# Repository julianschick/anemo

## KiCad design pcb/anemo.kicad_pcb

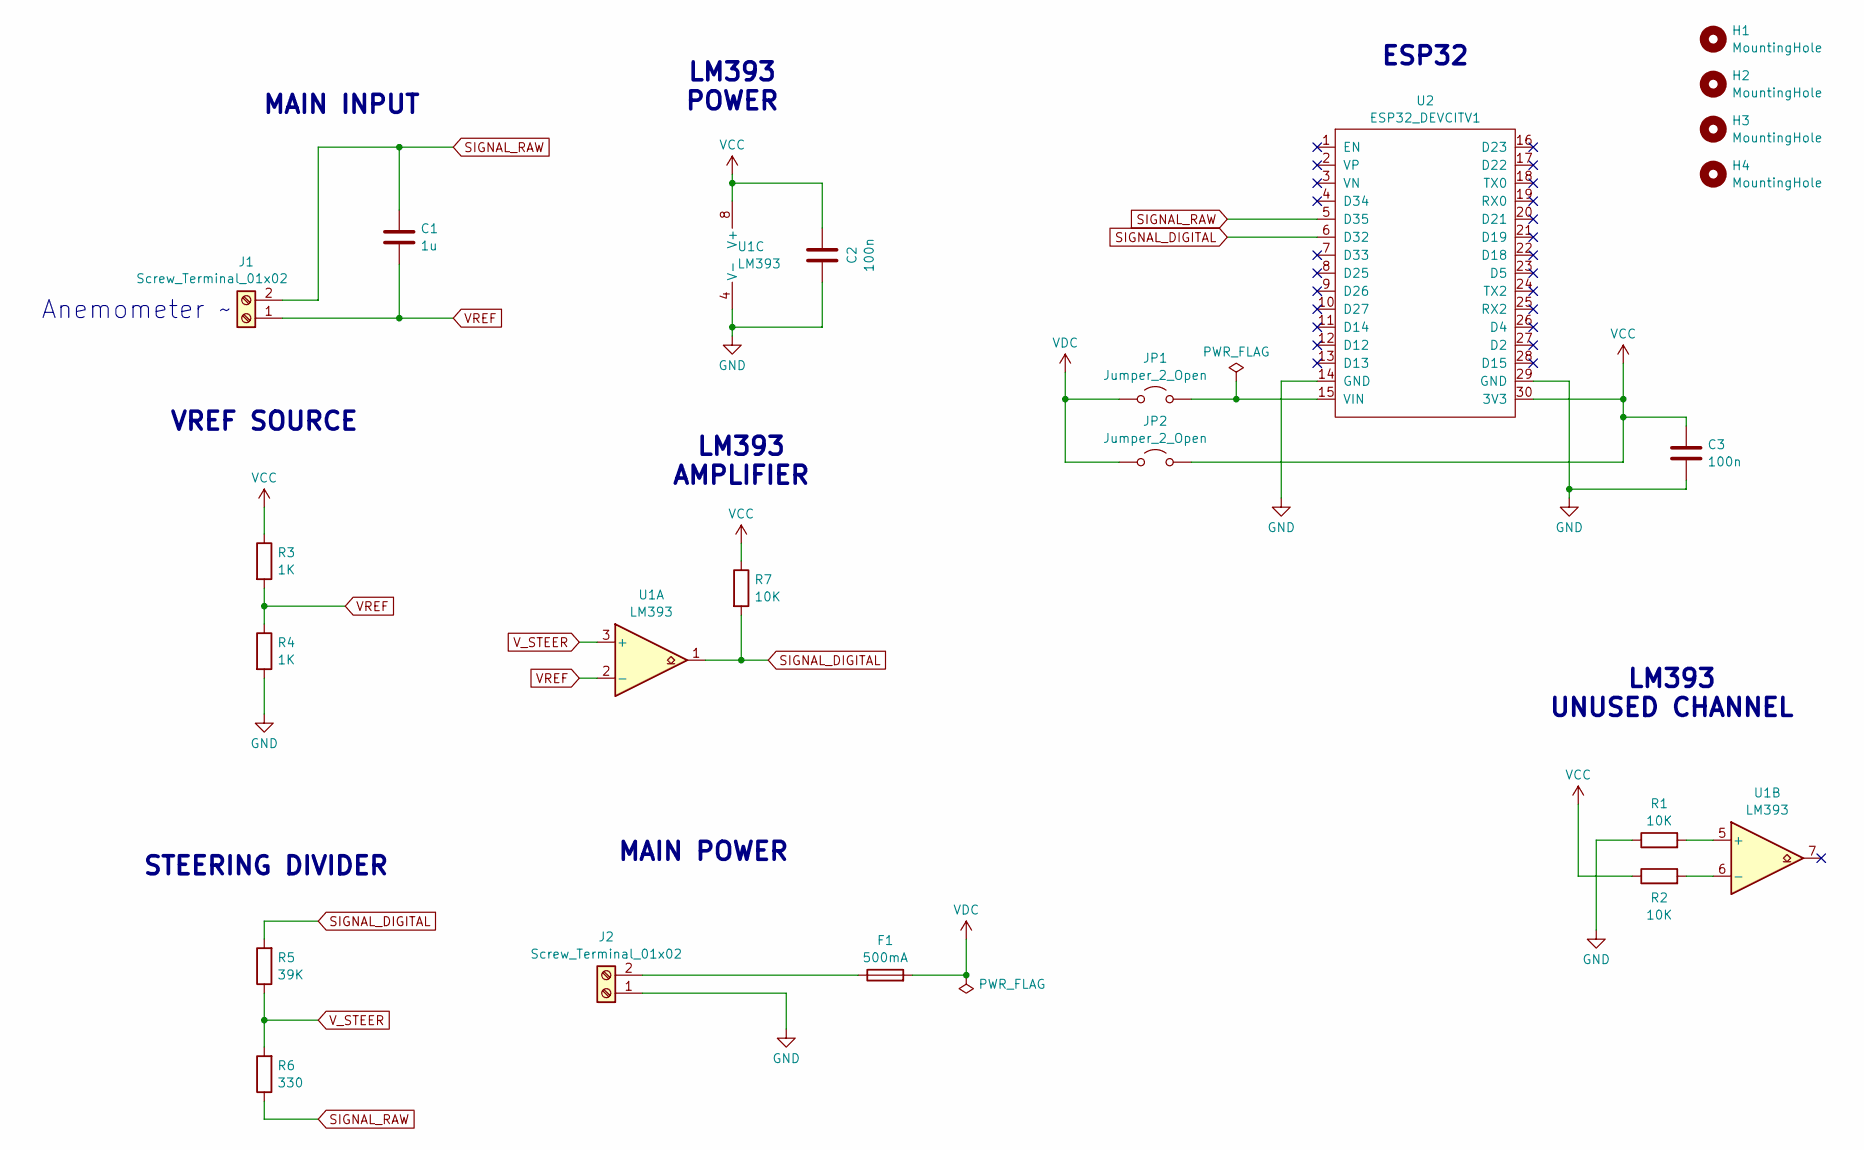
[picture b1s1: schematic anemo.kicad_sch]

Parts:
C1: 1u; C_Disc_D5.0mm_W2.5mm_P5.00mm
C2, C3: 100n; C_Disc_D5.0mm_W2.5mm_P5.00mm
F1: 500mA; Fuseholder_TR5_Littelfuse_No560_No460
H1, H2, H3, H4: MountingHole; MountingHole_3.2mm_M3_ISO7380
J1, J2: Screw_Terminal_01x02; TerminalBlock_MetzConnect_Type055_RT01502HDWU_1x02_P5.00mm_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
JP1, JP2: Jumper_2_Open; PinHeader_1x02_P2.54mm_Vertical
R1, R2, R7: 10K; R_Axial_DIN0207_L6.3mm_D2.5mm_P7.62mm_Horizontal
R3, R4: 1K; R_Axial_DIN0207_L6.3mm_D2.5mm_P7.62mm_Horizontal
R5: 39K; R_Axial_DIN0207_L6.3mm_D2.5mm_P7.62mm_Horizontal
R6: 330; R_Axial_DIN0207_L6.3mm_D2.5mm_P7.62mm_Horizontal
U1: LM393; DIP-8_W7.62mm
U2: ESP32_DEVCITV1; ESP32_DEVKITV1

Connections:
GND: C2.2, C3.2, J2.1, R1.1, R4.2, U1.4 (V-), U2.14 (GND), U2.29 (GND)
unnamed: F1.1, J2.2
unnamed: JP1.2 (B), U2.15 (VIN)
unnamed: R1.2, U1.5 (+)
unnamed: R2.2, U1.6 (-)
SIGNAL_DIGITAL: R5.2, R7.2, U1.1, U2.6 (D32)
SIGNAL_RAW: C1.1, J1.2, R6.1, U2.5 (D35)
VCC: C2.1, C3.1, JP2.2 (B), R2.1, R3.1, R7.1, U1.8 (V+), U2.30 (3V3)
VDC: F1.2, JP1.1 (A), JP2.1 (A)
VREF: C1.2, J1.1, R3.2, R4.1, U1.2 (-)
V_STEER: R5.1, R6.2, U1.3 (+)

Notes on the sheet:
LM393 POWER
ESP32
Anemometer ~
MAIN INPUT
STEERING DIVIDER
VREF SOURCE
LM393 AMPLIFIER
MAIN POWER
LM393 UNUSED CHANNEL

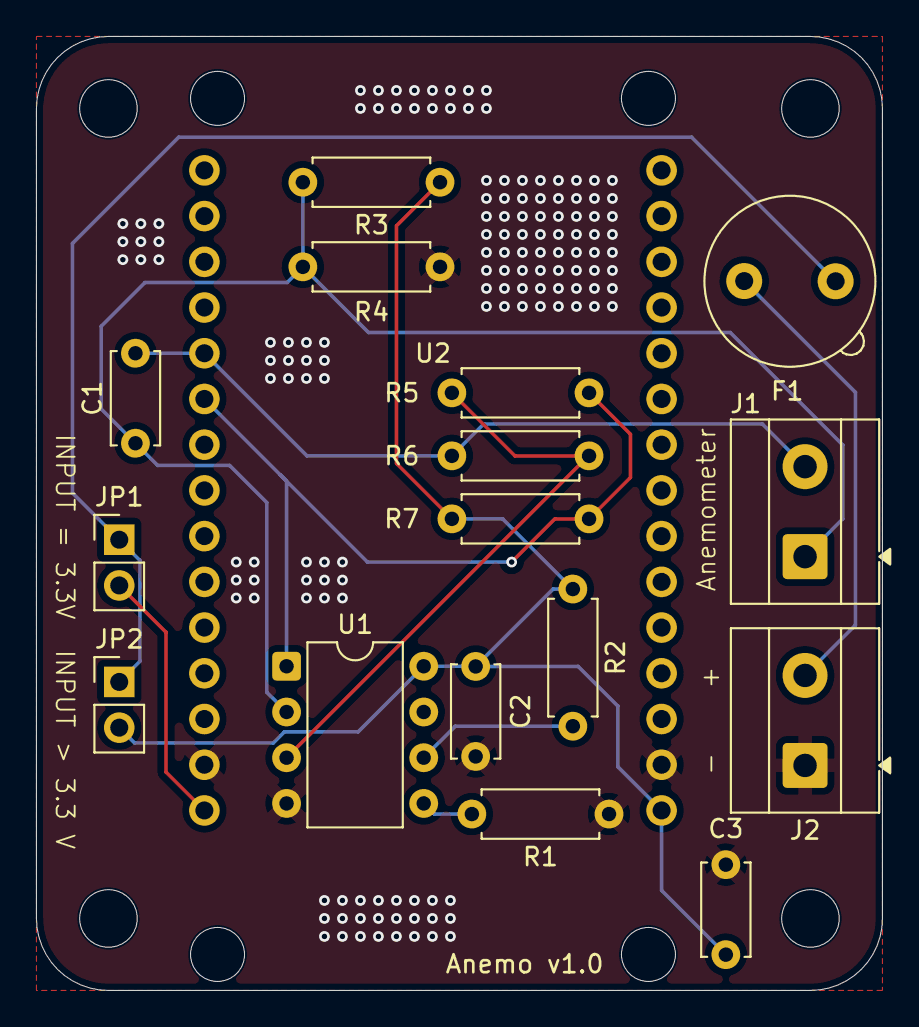
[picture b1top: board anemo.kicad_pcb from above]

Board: 2 copper layers, 47.0 x 53.0 mm, 21 parts (0 on the bottom side), 11 nets.

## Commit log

2025-07-16 initial
2026-02-22 oled display, calibration
2026-03-28 pcb to kicad10 format
2026-03-31 v1.0 gerber
